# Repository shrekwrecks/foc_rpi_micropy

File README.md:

hi if youre reviewing this thanks :]

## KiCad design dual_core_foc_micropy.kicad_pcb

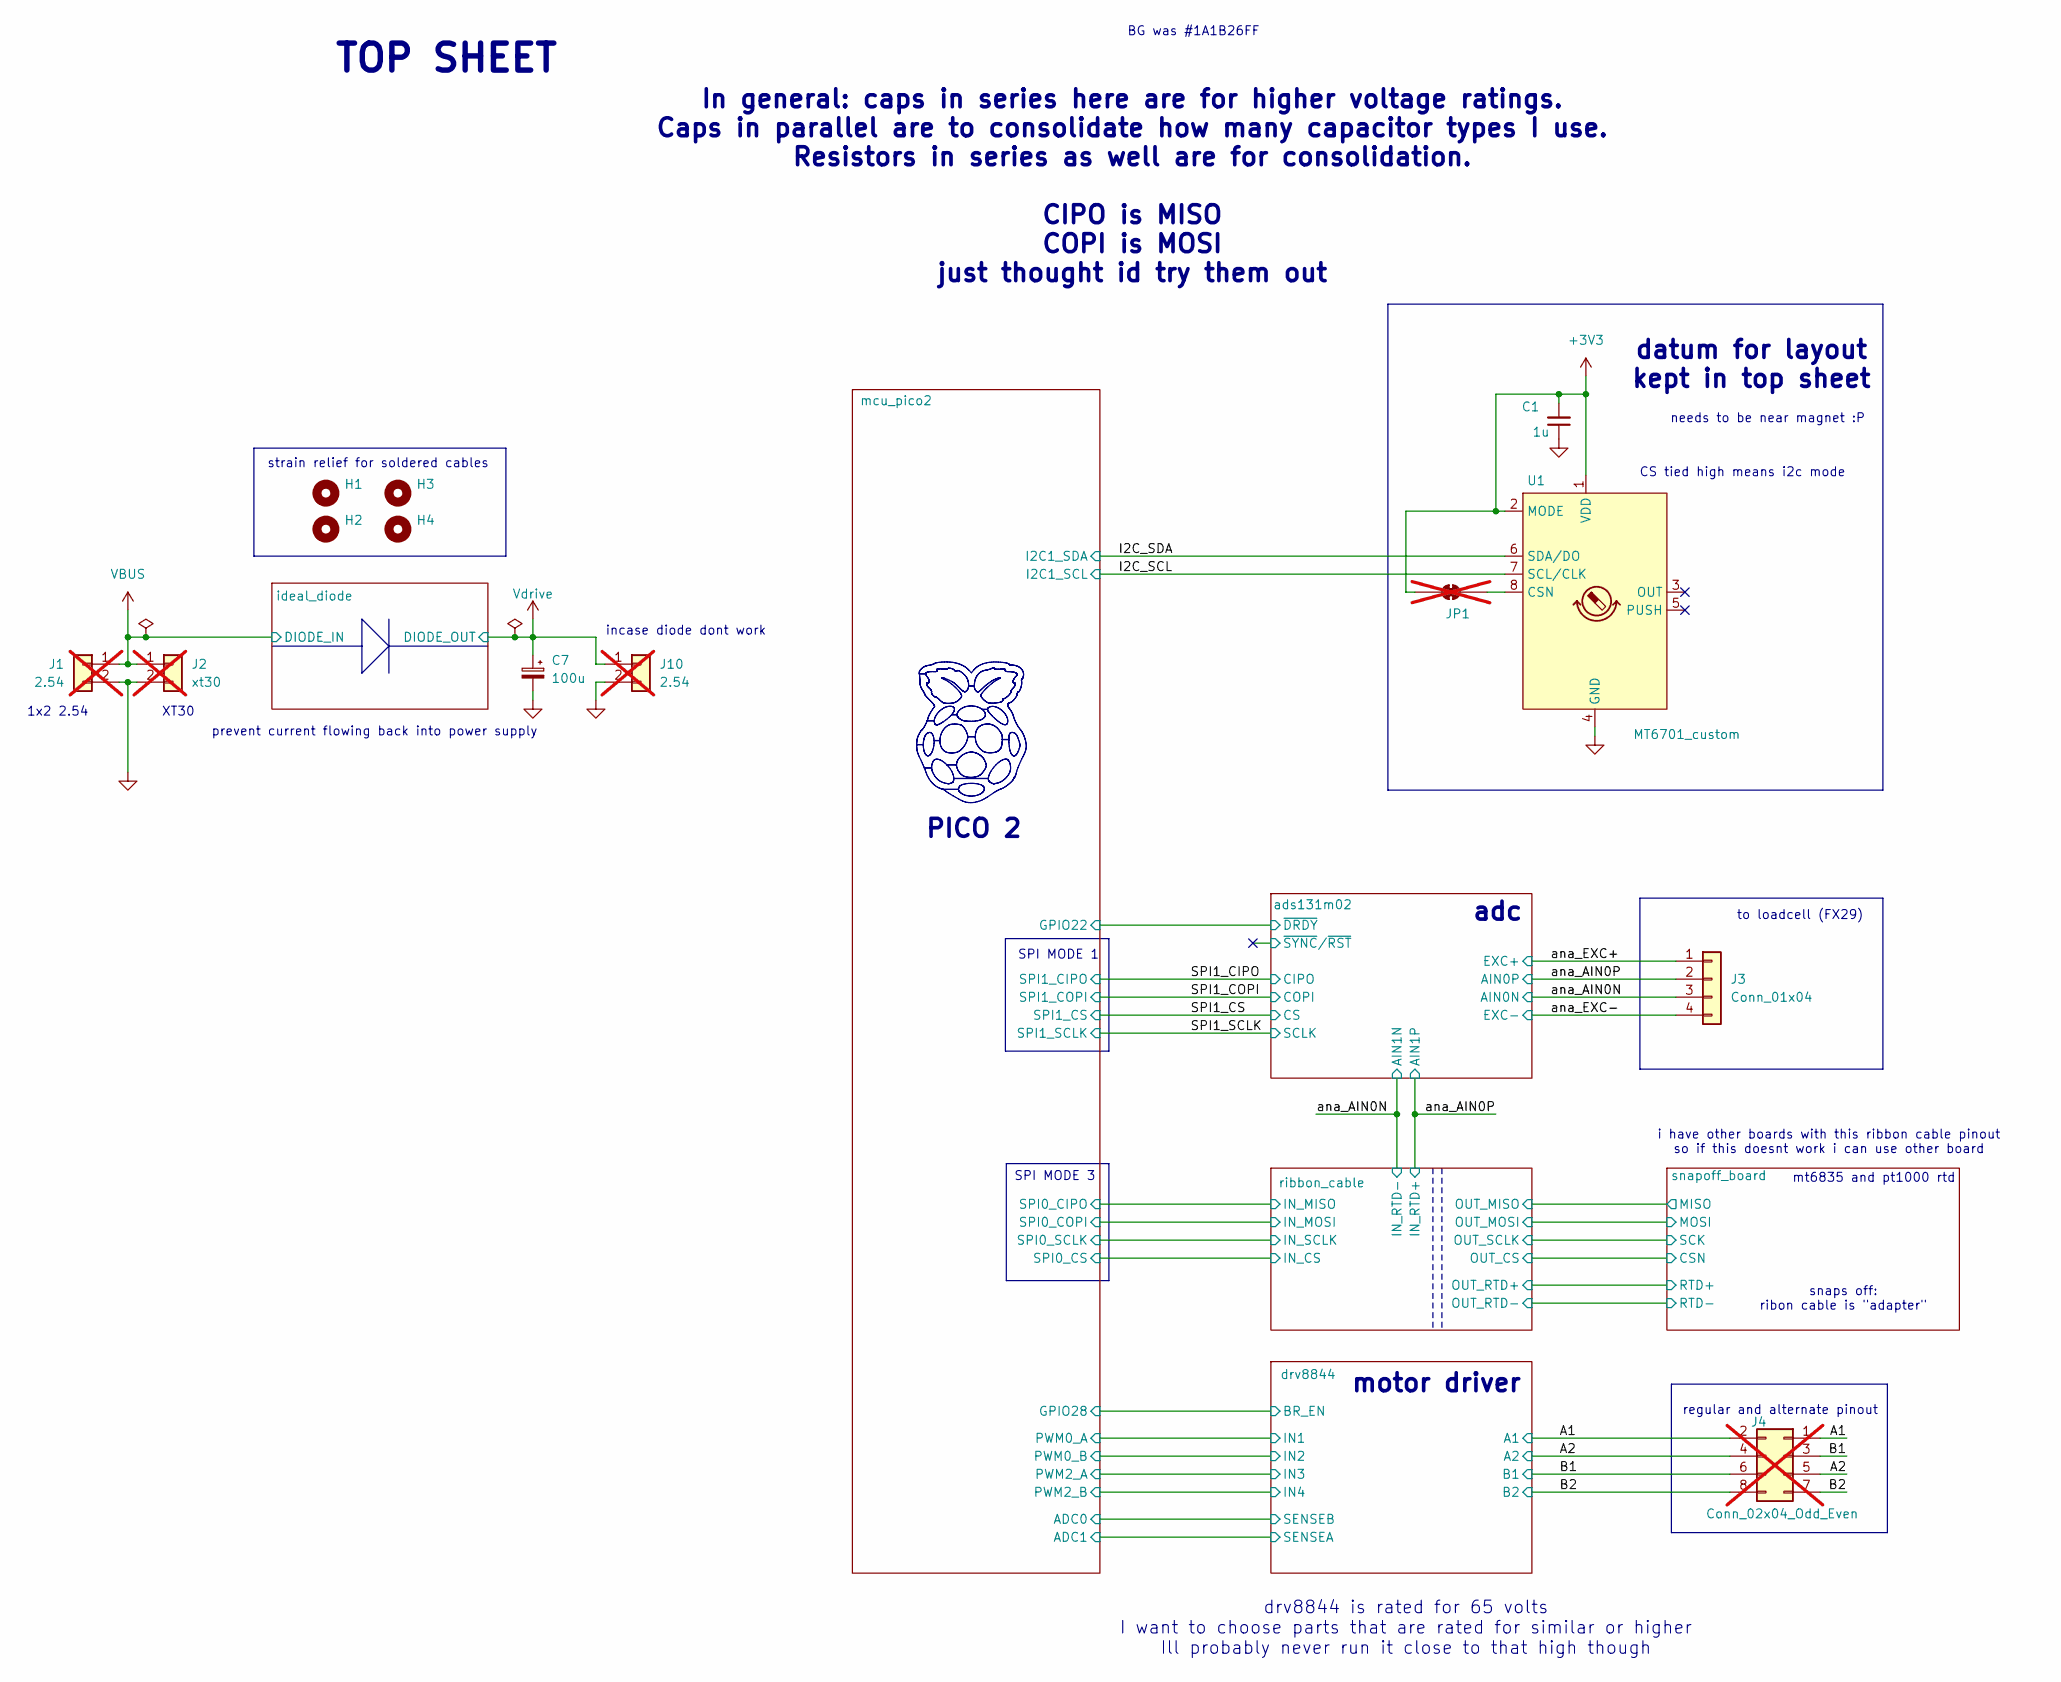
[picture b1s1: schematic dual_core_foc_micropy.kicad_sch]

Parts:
C1: 1u; C_0603_1608Metric; MPN CL10A105KB8NNNC
C7: 100u; CHEMI-KE0; MPN JVJ100V100M12X13
H1, H2, H3, H4: MountingHole; MountingHole_2.2mm_M2
J1, J10: 2.54; PinHeader_1x02_P2.54mm_Vertical; not fitted
J2: xt30; AMASS_XT30PW-M_1x02_P2.50mm_Horizontal; not fitted
J3: Conn_01x04; PinHeader_1x04_P2.54mm_Vertical
J4: Conn_02x04_Odd_Even; PinHeader_2x04_P2.54mm_Vertical; not fitted
JP1: SolderJumper_2_Bridged; SolderJumper-2_P1.3mm_Bridged_RoundedPad1.0x1.5mm; not fitted
U1: MT6701_custom; SO-8_3.9x4.9mm_P1.27mm; MPN MT6701CT-STD

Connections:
+3V3: C1.2, JP1.1 (A), U1.1 (VDD), U1.2 (MODE); also elsewhere on the board
/A1: J4.1, J4.2; also elsewhere on the board
/A2: J4.4, J4.5; also elsewhere on the board
/B1: J4.3, J4.6; also elsewhere on the board
/B2: J4.7, J4.8; also elsewhere on the board
/I2C_SCL: U1.7 (SCL/CLK); also elsewhere on the board
/I2C_SDA: U1.6 (SDA/DO); also elsewhere on the board
/ana_AIN0N: J3.3; also elsewhere on the board
/ana_AIN0P: J3.2; also elsewhere on the board
/ana_EXC+: J3.1; also elsewhere on the board
/ana_EXC-: J3.4; also elsewhere on the board
GND: C1.1, C7.2, J1.2, J2.2, J10.2, U1.4 (GND); also elsewhere on the board
unnamed: JP1.2 (B), U1.8 (CSN)
VBUS: J1.1, J2.1; also elsewhere on the board
Vdrive: C7.1, J10.1; also elsewhere on the board

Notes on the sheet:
snaps off: ribon cable is "adapter"
mt6835 and pt1000 rtd
i have other boards with this ribbon cable pinout so if this doesnt work i can use other board
regular and alternate pinout
TOP SHEET
prevent current flowing back into power supply
drv8844 is rated for 65 volts I want to choose parts that are rated for similar or higher Ill probably never run it close to that high though
In general: caps in series here are for higher voltage ratings. Caps in parallel are to consolidate how many capacitor types I use. Resistors in series as well are for consolidation. CIPO is MISO COPI is MOSI just thought id try them out
adc
1x2 2.54
strain relief for soldered cables
SPI MODE 1
needs to be near magnet :P
SPI MODE 3
CS tied high means i2c mode
PICO 2
incase diode dont work
XT30
datum for layout kept in top sheet
BG was #1A1B26FF
to loadcell (FX29)
motor driver

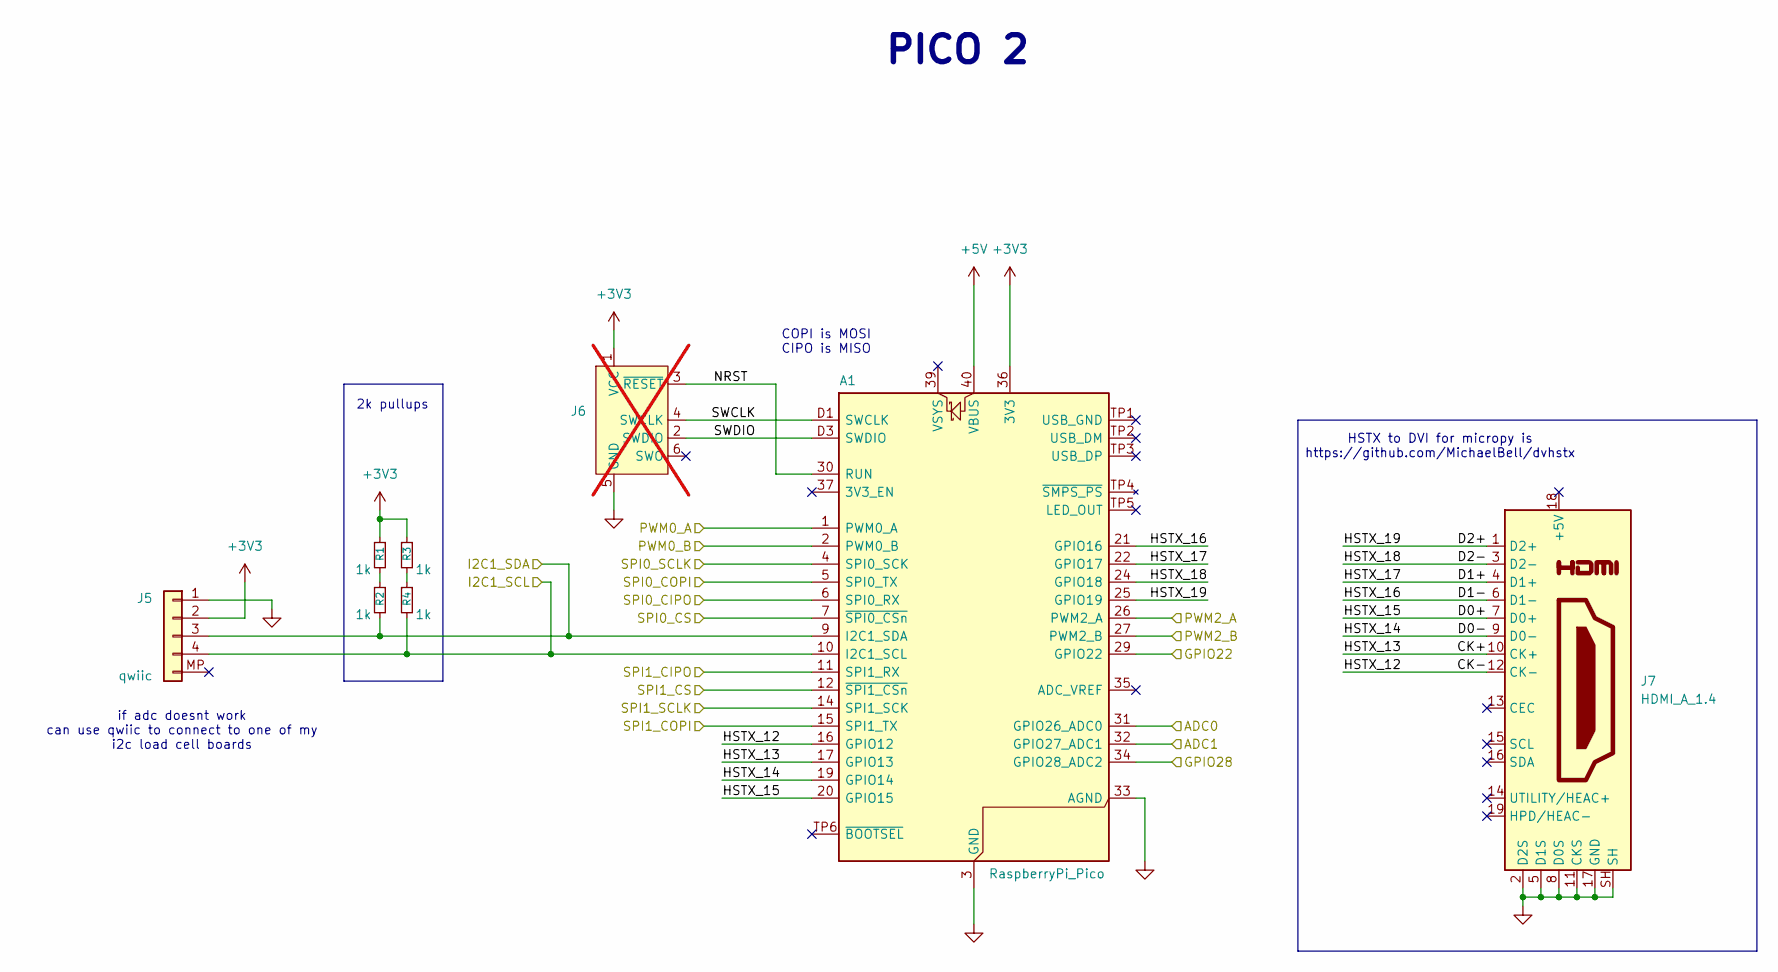
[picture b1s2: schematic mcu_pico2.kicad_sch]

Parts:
A1: RaspberryPi_Pico; RaspberryPi_Pico_SMD
J5: qwiic; JST_SH_BM04B-SRSS-TB_1x04-1MP_P1.00mm_Vertical; MPN BM04B-SRSS-TB(LF)(SN)
J6: Conn_ARM_SWD_TagConnect_TC2030-NL; Tag-Connect_TC2030-IDC-NL_2x03_P1.27mm_Vertical; not fitted
J7: HDMI_A_1.4; HDMI_A_Amphenol_10029449-x01xLF_Horizontal; MPN 10029449-111RLF
R1, R2, R3, R4: 1k; R_0402_1005Metric; MPN 0402WGF1001TCE

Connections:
+3V3: A1.36 (3V3), J5.2, J6.1 (VCC), R1.1, R3.1; also elsewhere on the board
+5V: A1.40 (VBUS)
/I2C_SCL: A1.10 (I2C1_SCL), J5.4, R4.2; also elsewhere on the board
/I2C_SDA: A1.9 (I2C1_SDA), J5.3, R2.2; also elsewhere on the board
/SPI1_CIPO: A1.11 (SPI1_RX); also elsewhere on the board
/SPI1_COPI: A1.15 (SPI1_TX); also elsewhere on the board
/SPI1_CS: A1.12 (~SPI1_CSn); also elsewhere on the board
/SPI1_SCLK: A1.14 (SPI1_SCK); also elsewhere on the board
/ads131m02/~DRDY: A1.29 (GPIO22); also elsewhere on the board
/drv8844/BR_EN: A1.34 (GPIO28_ADC2); also elsewhere on the board
/drv8844/IN1: A1.1 (PWM0_A); also elsewhere on the board
/drv8844/IN2: A1.2 (PWM0_B); also elsewhere on the board
/drv8844/IN3: A1.26 (PWM2_A); also elsewhere on the board
/drv8844/IN4: A1.27 (PWM2_B); also elsewhere on the board
/drv8844/SENSEA: A1.32 (GPIO27_ADC1); also elsewhere on the board
/drv8844/SENSEB: A1.31 (GPIO26_ADC0); also elsewhere on the board
/mcu_pico2/CK+: A1.17 (GPIO13), J7.10 (CK+)
/mcu_pico2/CK-: A1.16 (GPIO12), J7.12 (CK-)
/mcu_pico2/D0+: A1.20 (GPIO15), J7.7 (D0+)
/mcu_pico2/D0-: A1.19 (GPIO14), J7.9 (D0-)
/mcu_pico2/D1+: A1.22 (GPIO17), J7.4 (D1+)
/mcu_pico2/D1-: A1.21 (GPIO16), J7.6 (D1-)
/mcu_pico2/D2+: A1.25 (GPIO19), J7.1 (D2+)
/mcu_pico2/D2-: A1.24 (GPIO18), J7.3 (D2-)
/mcu_pico2/NRST: A1.30 (RUN), J6.3 (~RESET)
/mcu_pico2/SPI0_CIPO: A1.6 (SPI0_RX); also elsewhere on the board
/mcu_pico2/SPI0_COPI: A1.5 (SPI0_TX); also elsewhere on the board
/mcu_pico2/SPI0_CS: A1.7 (~SPI0_CSn); also elsewhere on the board
/mcu_pico2/SPI0_SCLK: A1.4 (SPI0_SCK); also elsewhere on the board
/mcu_pico2/SWCLK: A1.D1 (SWCLK), J6.4 (SWCLK)
/mcu_pico2/SWDIO: A1.D3 (SWDIO), J6.2 (SWDIO)
GND: A1.3 (GND), A1.8 (GND), A1.13 (GND), A1.18 (GND), A1.23 (GND), A1.28 (GND), A1.33 (AGND), A1.38 (GND), A1.D2 (GND), J5.1, J6.5 (GND), J7.2 (D2S), J7.5 (D1S), J7.8 (D0S), J7.11 (CKS), J7.17 (GND), J7.SH; also elsewhere on the board
unnamed: R1.2, R2.1
unnamed: R3.2, R4.1

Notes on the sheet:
PICO 2
HSTX to DVI for micropy is https://github.com/MichaelBell/dvhstx
2k pullups
COPI is MOSI CIPO is MISO
if adc doesnt work can use qwiic to connect to one of my i2c load cell boards

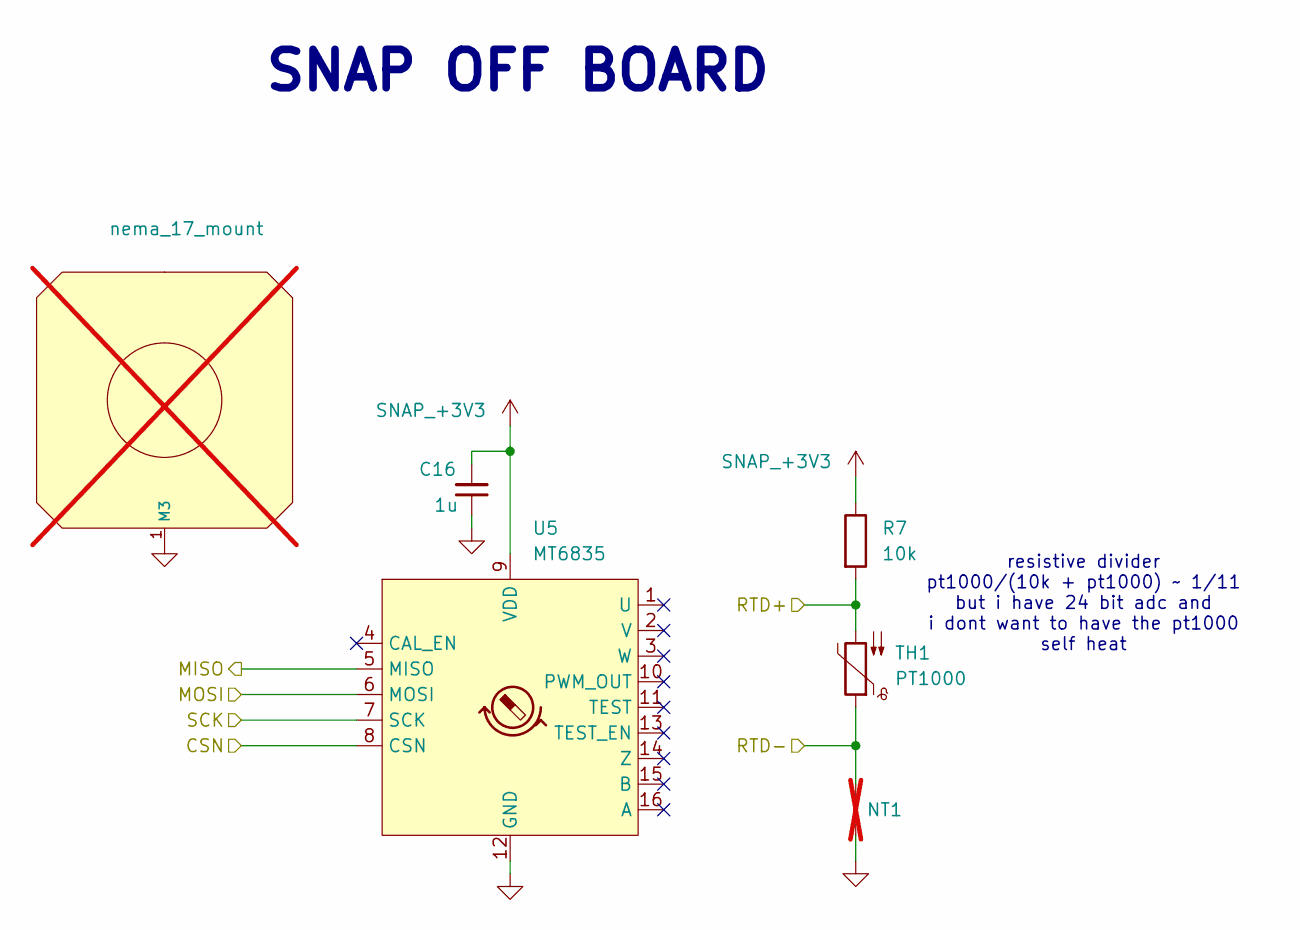
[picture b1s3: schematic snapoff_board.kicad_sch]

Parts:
C16: 1u; C_0603_1608Metric; MPN CL10A105KB8NNNC
MNT1: nema_17_mount; not fitted
NT1: NetTie_2; NetTie-2_SMD_Pad0.5mm; not fitted
R7: 10k; R_0805_2012Metric_Pad1.20x1.40mm_HandSolder; MPN 0805W8F1002T5E
TH1: PT1000; R_0805_2012Metric; MPN 32207615
U5: MT6835; mt6835; MPN MT6835GT-STD-R

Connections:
/ribbon_cable/OUT_CS: U5.8 (CSN); also elsewhere on the board
/ribbon_cable/OUT_MISO: U5.5 (MISO); also elsewhere on the board
/ribbon_cable/OUT_MOSI: U5.6 (MOSI); also elsewhere on the board
/ribbon_cable/OUT_RTD+: R7.2, TH1.2; also elsewhere on the board
/ribbon_cable/OUT_RTD-: NT1.2, TH1.1; also elsewhere on the board
/ribbon_cable/OUT_SCLK: U5.7 (SCK); also elsewhere on the board
GND: C16.1, MNT1.1 (M3_1), NT1.1, U5.12 (GND); also elsewhere on the board
SNAP_+3V3: C16.2, R7.1, U5.9 (VDD); also elsewhere on the board

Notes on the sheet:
resistive divider pt1000/(10k + pt1000) ~ 1/11 but i have 24 bit adc and i dont want to have the pt1000 self heat
SNAP OFF BOARD

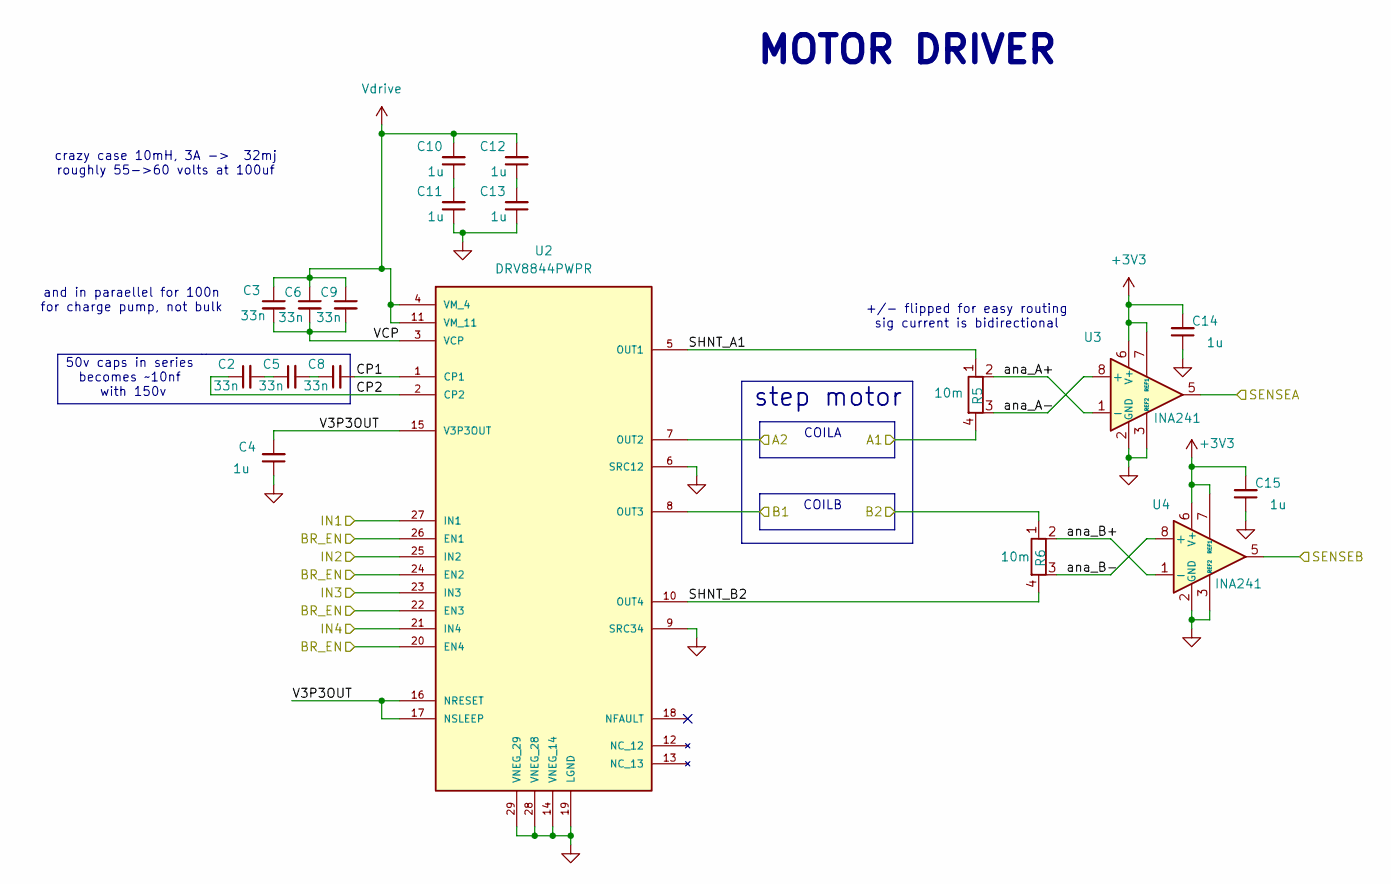
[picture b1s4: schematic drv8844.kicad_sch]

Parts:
C2, C3, C5, C6, C8, C9: 33n; C_0603_1608Metric; MPN CL10B333KB8NNNC
C4, C10, C11, C12, C13, C14, C15: 1u; C_0603_1608Metric; MPN CL10A105KB8NNNC
R5, R6: 10m; R_1206_resistor_6_pad_kelvin; MPN FRM121WFR010TM
U2: DRV8844PWPR; IC_DRV8844PWPR; PARTREV D
U3, U4: INA241; SOT-23-8; MPN INA241A3IDDFR

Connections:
+3V3: C14.2, C15.2, U3.6 (V+), U3.7 (REF1), U4.6 (V+), U4.7 (REF1); also elsewhere on the board
/A1: R5.4; also elsewhere on the board
/A2: U2.7 (OUT2); also elsewhere on the board
/B1: U2.8 (OUT3); also elsewhere on the board
/B2: R6.1; also elsewhere on the board
/drv8844/BR_EN: U2.20 (EN4), U2.22 (EN3), U2.24 (EN2), U2.26 (EN1); also elsewhere on the board
/drv8844/CP1: C8.2, U2.1 (CP1)
/drv8844/CP2: C2.1, U2.2 (CP2)
/drv8844/IN1: U2.27 (IN1); also elsewhere on the board
/drv8844/IN2: U2.25 (IN2); also elsewhere on the board
/drv8844/IN3: U2.23 (IN3); also elsewhere on the board
/drv8844/IN4: U2.21 (IN4); also elsewhere on the board
/drv8844/SENSEA: U3.5; also elsewhere on the board
/drv8844/SENSEB: U4.5; also elsewhere on the board
/drv8844/SHNT_A1: R5.1, U2.5 (OUT1)
/drv8844/SHNT_B2: R6.4, U2.10 (OUT4)
/drv8844/V3P3OUT: C4.2, U2.15 (V3P3OUT), U2.16 (NRESET), U2.17 (NSLEEP)
/drv8844/VCP: C3.2, C6.2, C9.2, U2.3 (VCP)
/drv8844/ana_A+: R5.2, U3.1 (-)
/drv8844/ana_A-: R5.3, U3.8 (+)
/drv8844/ana_B+: R6.2, U4.1 (-)
/drv8844/ana_B-: R6.3, U4.8 (+)
GND: C4.1, C11.1, C13.1, C14.1, C15.1, U2.6 (SRC12), U2.9 (SRC34), U2.14 (VNEG_14), U2.19 (LGND), U2.28 (VNEG_28), U2.29 (VNEG_29), U3.2 (GND), U3.3 (REF2), U3.4 (GND), U4.2 (GND), U4.3 (REF2), U4.4 (GND); also elsewhere on the board
unnamed: C2.2, C5.1
unnamed: C5.2, C8.1
unnamed: C10.1, C11.2
unnamed: C12.1, C13.2
Vdrive: C3.1, C6.1, C9.1, C10.2, C12.2, U2.4 (VM_4), U2.11 (VM_11); also elsewhere on the board

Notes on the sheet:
crazy case 10mH, 3A -> 32mj roughly 55->60 volts at 100uf
50v caps in series becomes ~10nf with 150v
COILA
COILB
and in paraellel for 100n for charge pump, not bulk
step motor
+/- flipped for easy routing sig current is bidirectional
MOTOR DRIVER

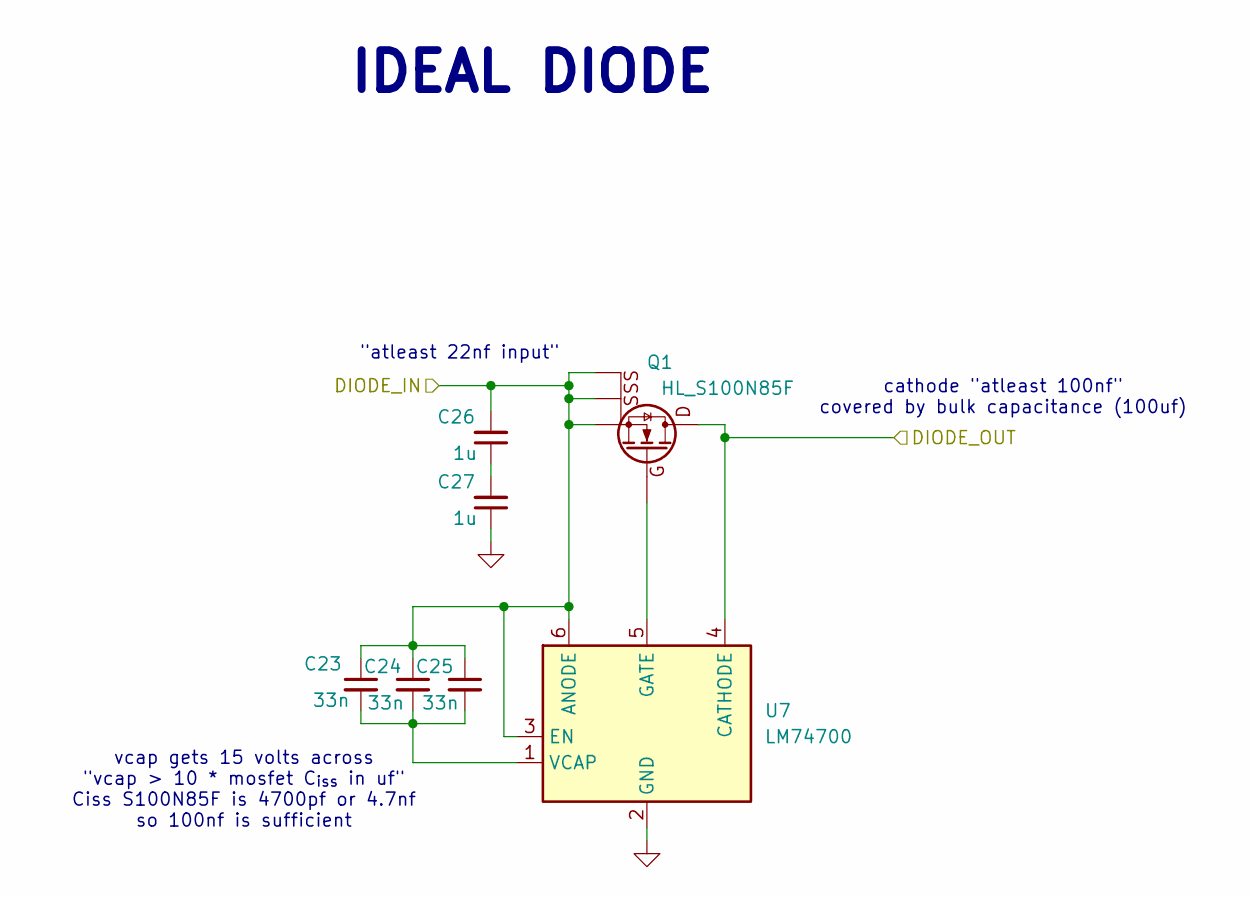
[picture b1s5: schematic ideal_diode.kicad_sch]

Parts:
C23, C24, C25: 33n; C_0603_1608Metric; MPN CL10B333KB8NNNC
C26, C27: 1u; C_0603_1608Metric; MPN CL10A105KB8NNNC
Q1: HL_S100N85F; PQFN-8-EP_6x5mm_P1.27mm_Generic; MPN S100N85F
U7: LM74700; SOT-23-6

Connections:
GND: C27.1, U7.2 (GND); also elsewhere on the board
unnamed: C26.1, C27.2
unnamed: Q1.4 (G), U7.5 (GATE)
unnamed: C23.2, C24.2, C25.2, U7.1 (VCAP)
VBUS: C23.1, C24.1, C25.1, C26.2, Q1.1 (S), Q1.2 (S), Q1.3 (S), U7.3 (EN), U7.6 (ANODE); also elsewhere on the board
Vdrive: Q1.5 (D), U7.4 (CATHODE); also elsewhere on the board

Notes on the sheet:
cathode "atleast 100nf" covered by bulk capacitance (100uf)
"atleast 22nf input"
vcap gets 15 volts across "vcap > 10 * mosfet C_{iss} in uf" Ciss S100N85F is 4700pf or 4.7nf so 100nf is sufficient
IDEAL DIODE

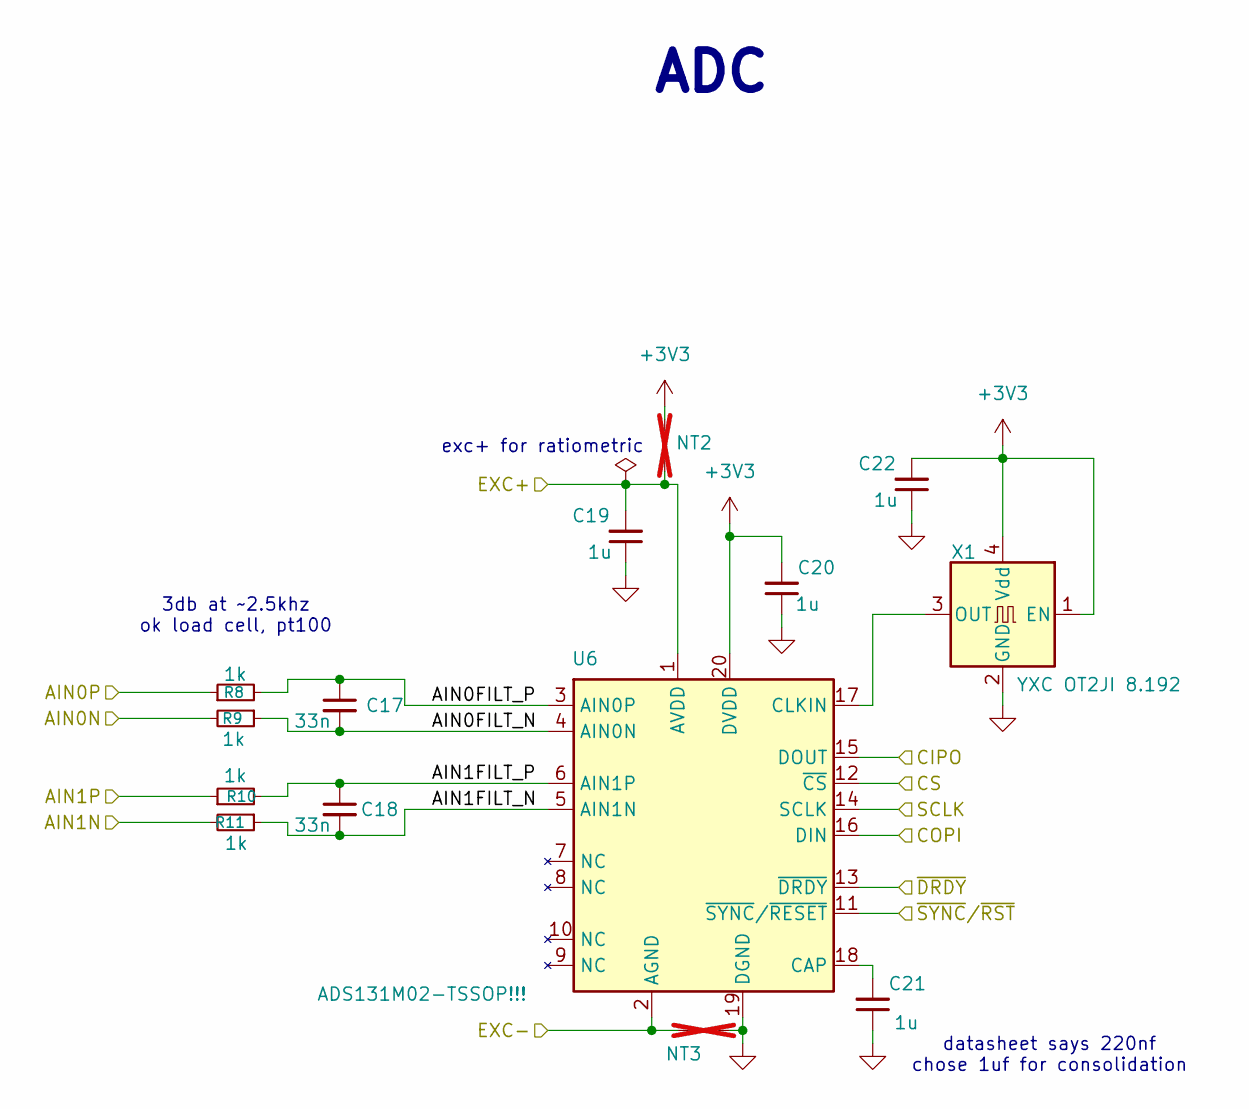
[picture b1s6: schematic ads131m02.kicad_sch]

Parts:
C17, C18: 33n; C_0603_1608Metric; MPN CL10B333KB8NNNC
C19, C20, C21, C22: 1u; C_0603_1608Metric; MPN CL10A105KB8NNNC
NT2, NT3: NetTie_2; NetTie-2_SMD_Pad0.5mm; not fitted
R8, R9, R10, R11: 1k; R_0402_1005Metric; MPN 0402WGF1001TCE
U6: ADS131M02-TSSOP!!!; TSSOP-20_4.4x6.5mm_P0.65mm; MPN ADS131M02IPWR
X1: YXC OT2JI 8.192; Oscillator_SMD_Abracon_ASE-4Pin_3.2x2.5mm; MPN OT2JI-111-8.192M

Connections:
+3V3: C20.2, C22.2, NT2.2, U6.20 (DVDD), X1.1 (EN), X1.4 (Vdd); also elsewhere on the board
/SPI1_CIPO: U6.15 (DOUT); also elsewhere on the board
/SPI1_COPI: U6.16 (DIN); also elsewhere on the board
/SPI1_CS: U6.12 (~CS); also elsewhere on the board
/SPI1_SCLK: U6.14 (SCLK); also elsewhere on the board
/ads131m02/AIN0FILT_N: C17.2, R9.1, U6.4 (AIN0N)
/ads131m02/AIN0FILT_P: C17.1, R8.2, U6.3 (AIN0P)
/ads131m02/AIN1FILT_N: C18.2, R11.1, U6.5 (AIN1N)
/ads131m02/AIN1FILT_P: C18.1, R10.2, U6.6 (AIN1P)
/ads131m02/~DRDY: U6.13 (~DRDY); also elsewhere on the board
/ads131m02/~SYNC/~RST: U6.11 (~SYNC/~RESET)
/ana_AIN0N: R9.2, R11.2; also elsewhere on the board
/ana_AIN0P: R8.1, R10.1; also elsewhere on the board
/ana_EXC+: C19.2, NT2.1, U6.1 (AVDD); also elsewhere on the board
/ana_EXC-: NT3.2, U6.2 (AGND); also elsewhere on the board
GND: C19.1, C20.1, C21.1, C22.1, NT3.1, U6.19 (DGND), X1.2 (GND); also elsewhere on the board
unnamed: C21.2, U6.18 (CAP)
unnamed: U6.17 (CLKIN), X1.3 (OUT)

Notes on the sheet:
ADC
datasheet says 220nf chose 1uf for consolidation
3db at ~2.5khz ok load cell, pt100
exc+ for ratiometric

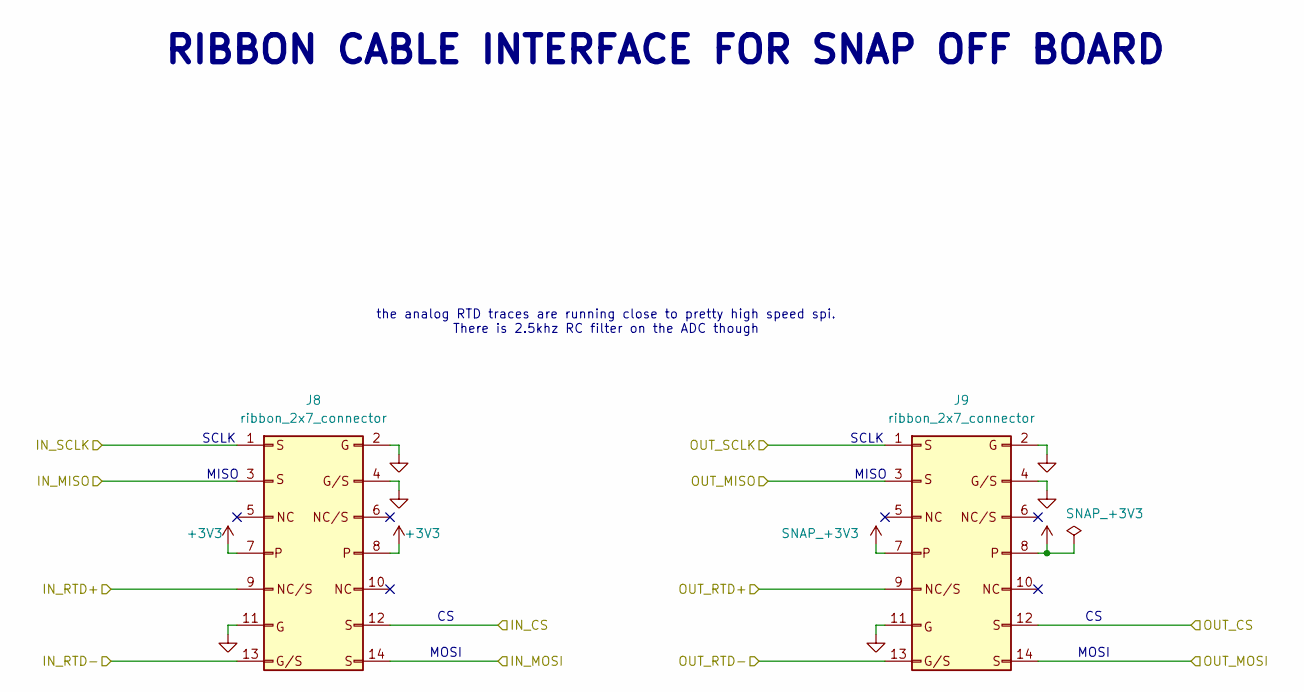
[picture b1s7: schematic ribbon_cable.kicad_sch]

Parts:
J8, J9: ribbon_2x7_connector; idc_1.27_smd_2x7

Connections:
+3V3: J8.7, J8.8; also elsewhere on the board
/ana_AIN0N: J8.13; also elsewhere on the board
/ana_AIN0P: J8.9; also elsewhere on the board
/mcu_pico2/SPI0_CIPO: J8.3; also elsewhere on the board
/mcu_pico2/SPI0_COPI: J8.14; also elsewhere on the board
/mcu_pico2/SPI0_CS: J8.12; also elsewhere on the board
/mcu_pico2/SPI0_SCLK: J8.1; also elsewhere on the board
/ribbon_cable/OUT_CS: J9.12; also elsewhere on the board
/ribbon_cable/OUT_MISO: J9.3; also elsewhere on the board
/ribbon_cable/OUT_MOSI: J9.14; also elsewhere on the board
/ribbon_cable/OUT_RTD+: J9.9; also elsewhere on the board
/ribbon_cable/OUT_RTD-: J9.13; also elsewhere on the board
/ribbon_cable/OUT_SCLK: J9.1; also elsewhere on the board
GND: J8.2, J8.4, J8.11, J9.2, J9.4, J9.11; also elsewhere on the board
SNAP_+3V3: J9.7, J9.8; also elsewhere on the board

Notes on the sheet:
MOSI
RIBBON CABLE INTERFACE FOR SNAP OFF BOARD
MISO
the analog RTD traces are running close to pretty high speed spi. There is 2.5khz RC filter on the ADC though
SCLK

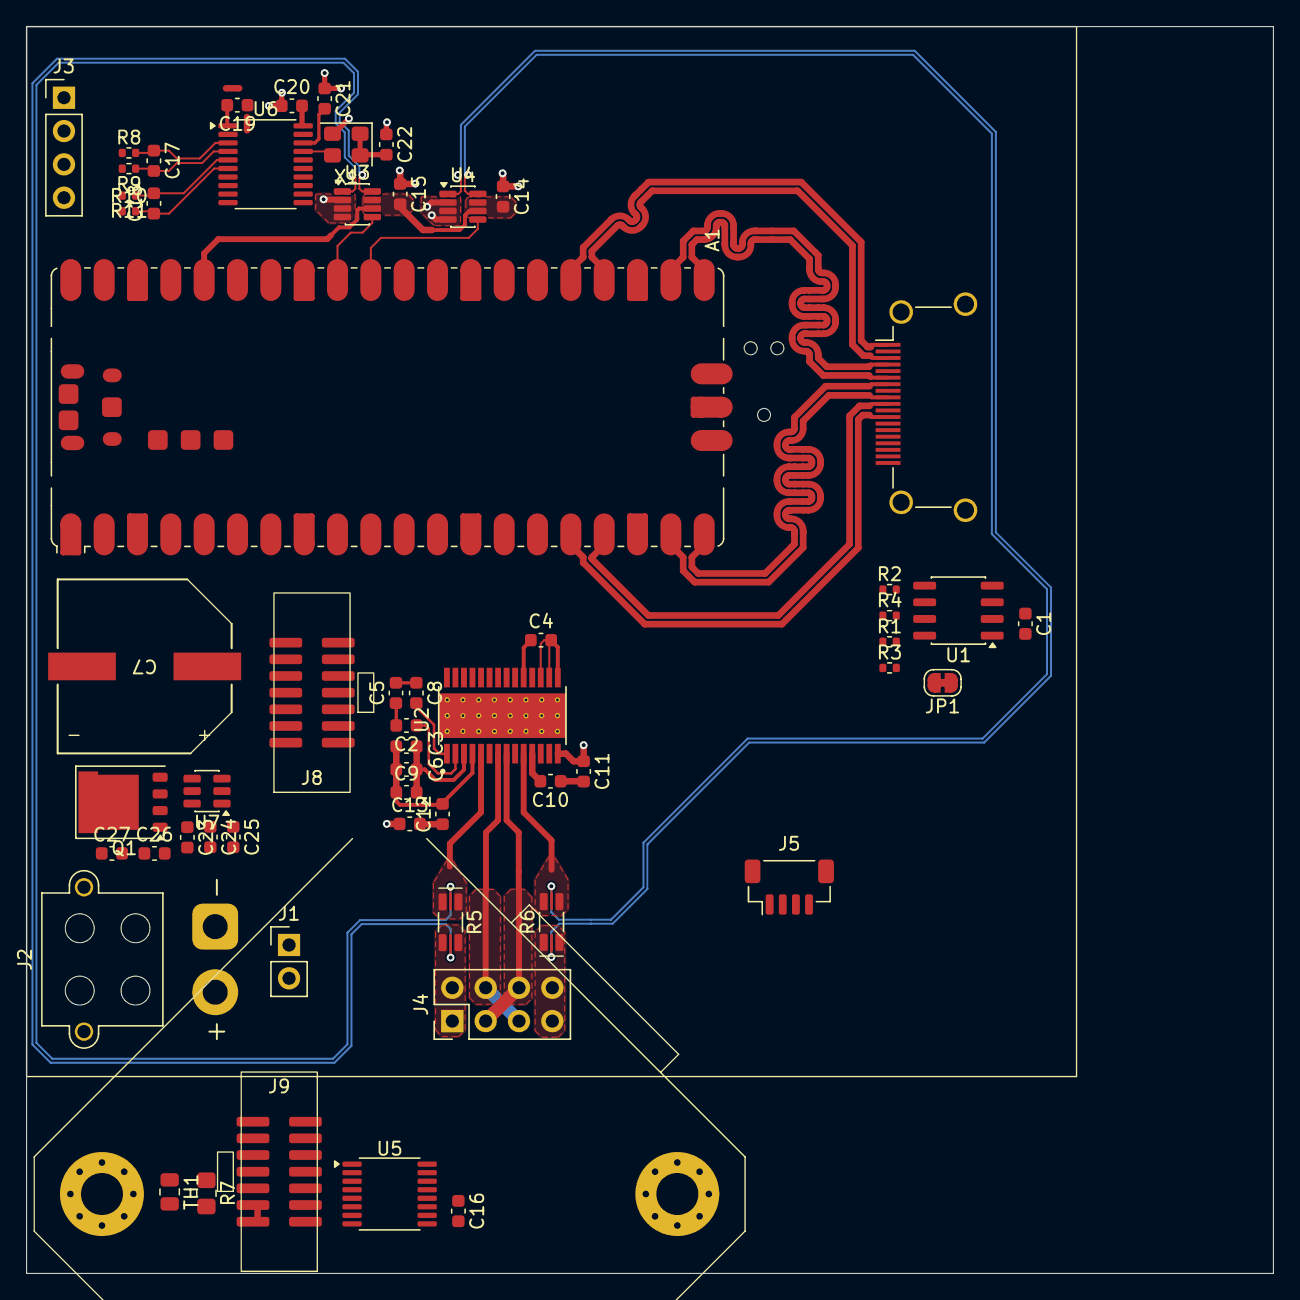
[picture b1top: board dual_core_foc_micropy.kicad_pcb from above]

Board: 2 copper layers, 95.0 x 95.0 mm, 67 parts (1 on the bottom side), 74 nets.
